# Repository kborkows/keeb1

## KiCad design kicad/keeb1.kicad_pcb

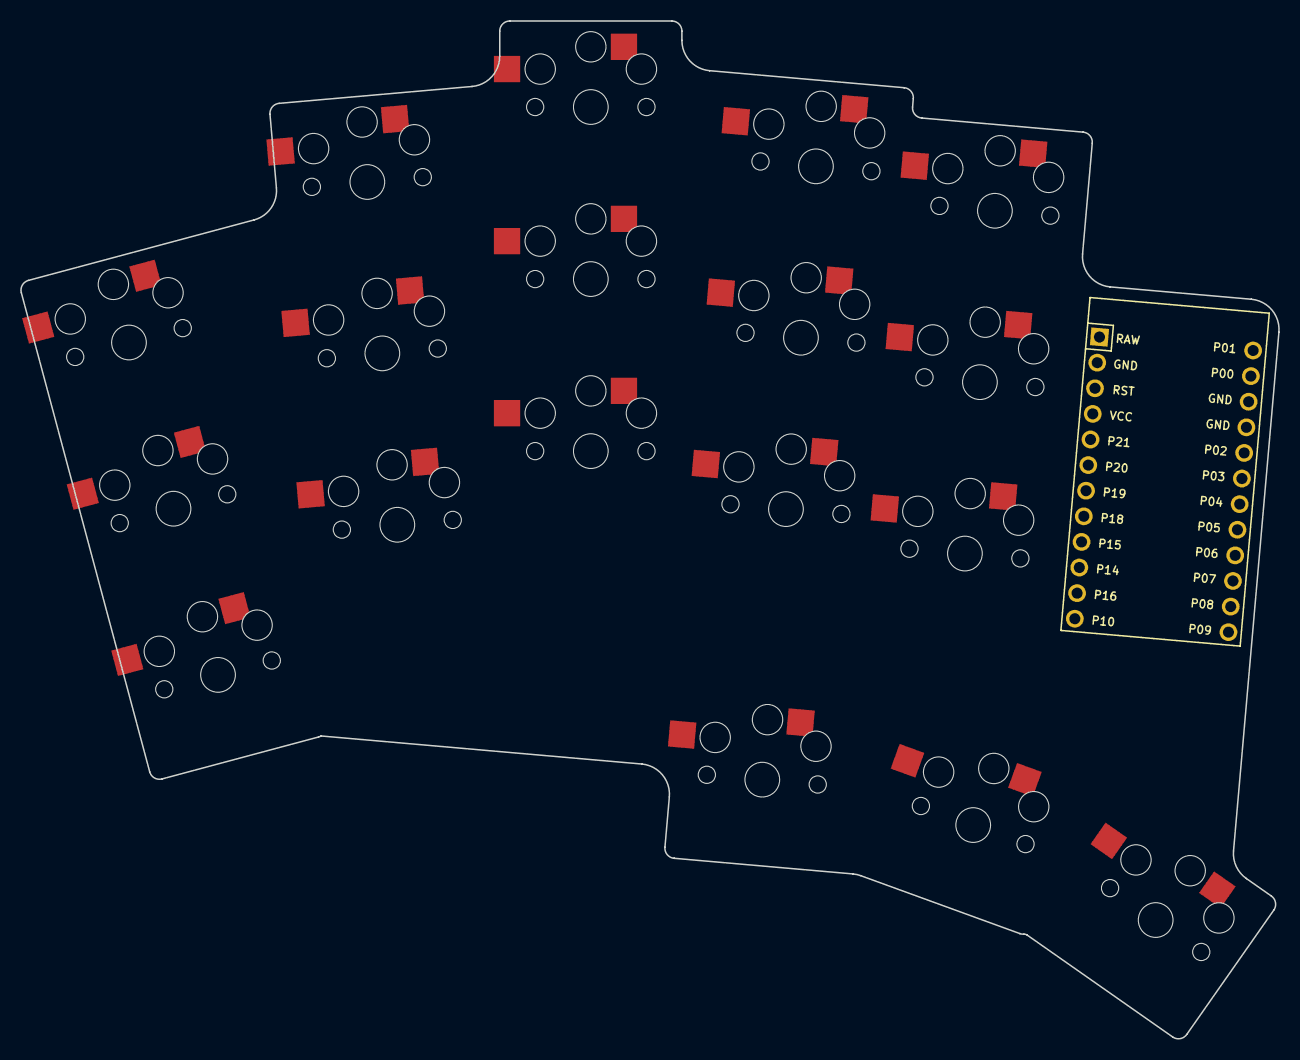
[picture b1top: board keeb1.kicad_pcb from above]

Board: 2 copper layers, 124.3 x 100.6 mm, 19 parts (0 on the bottom side), 18 nets, no tracks yet.

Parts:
MCU1: ProMicro
S1, S2, S3, S4, S5, S6, S7, S8, S9, S10, S11, S12, S13, S14, S15, S16, S17, S18: PG1350

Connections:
GND: MCU1.2, MCU1.15, MCU1.16, S1.2, S2.2, S3.2, S4.2, S5.2, S6.2, S7.2, S8.2, S9.2, S10.2, S11.2, S12.2, S13.2, S14.2, S15.2, S16.2, S17.2, S18.2
P0: MCU1.14, S6.1
P1: MCU1.13, S7.1
P3: MCU1.18, S5.1
P4: MCU1.19, S4.1
P5: MCU1.20, S3.1
P6: MCU1.21, S2.1
P7: MCU1.22, S1.1, S16.1
P8: MCU1.23, S17.1
P9: MCU1.24, S18.1
P10: MCU1.12, S13.1
P14: MCU1.10, S11.1
P15: MCU1.9, S10.1
P16: MCU1.11, S12.1
P18: MCU1.8, S9.1
P19: MCU1.7, S8.1
P20: MCU1.6, S14.1
P21: MCU1.5, S15.1

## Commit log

2022-11-13 Add initial config and helper scripts
2022-11-13 Add .gitignore
2022-11-13 Add placeholder kicad project
2022-11-13 Adjust outline
2022-11-13 Commit exported kicad files
2022-11-13 git-ignore kicad backup files
